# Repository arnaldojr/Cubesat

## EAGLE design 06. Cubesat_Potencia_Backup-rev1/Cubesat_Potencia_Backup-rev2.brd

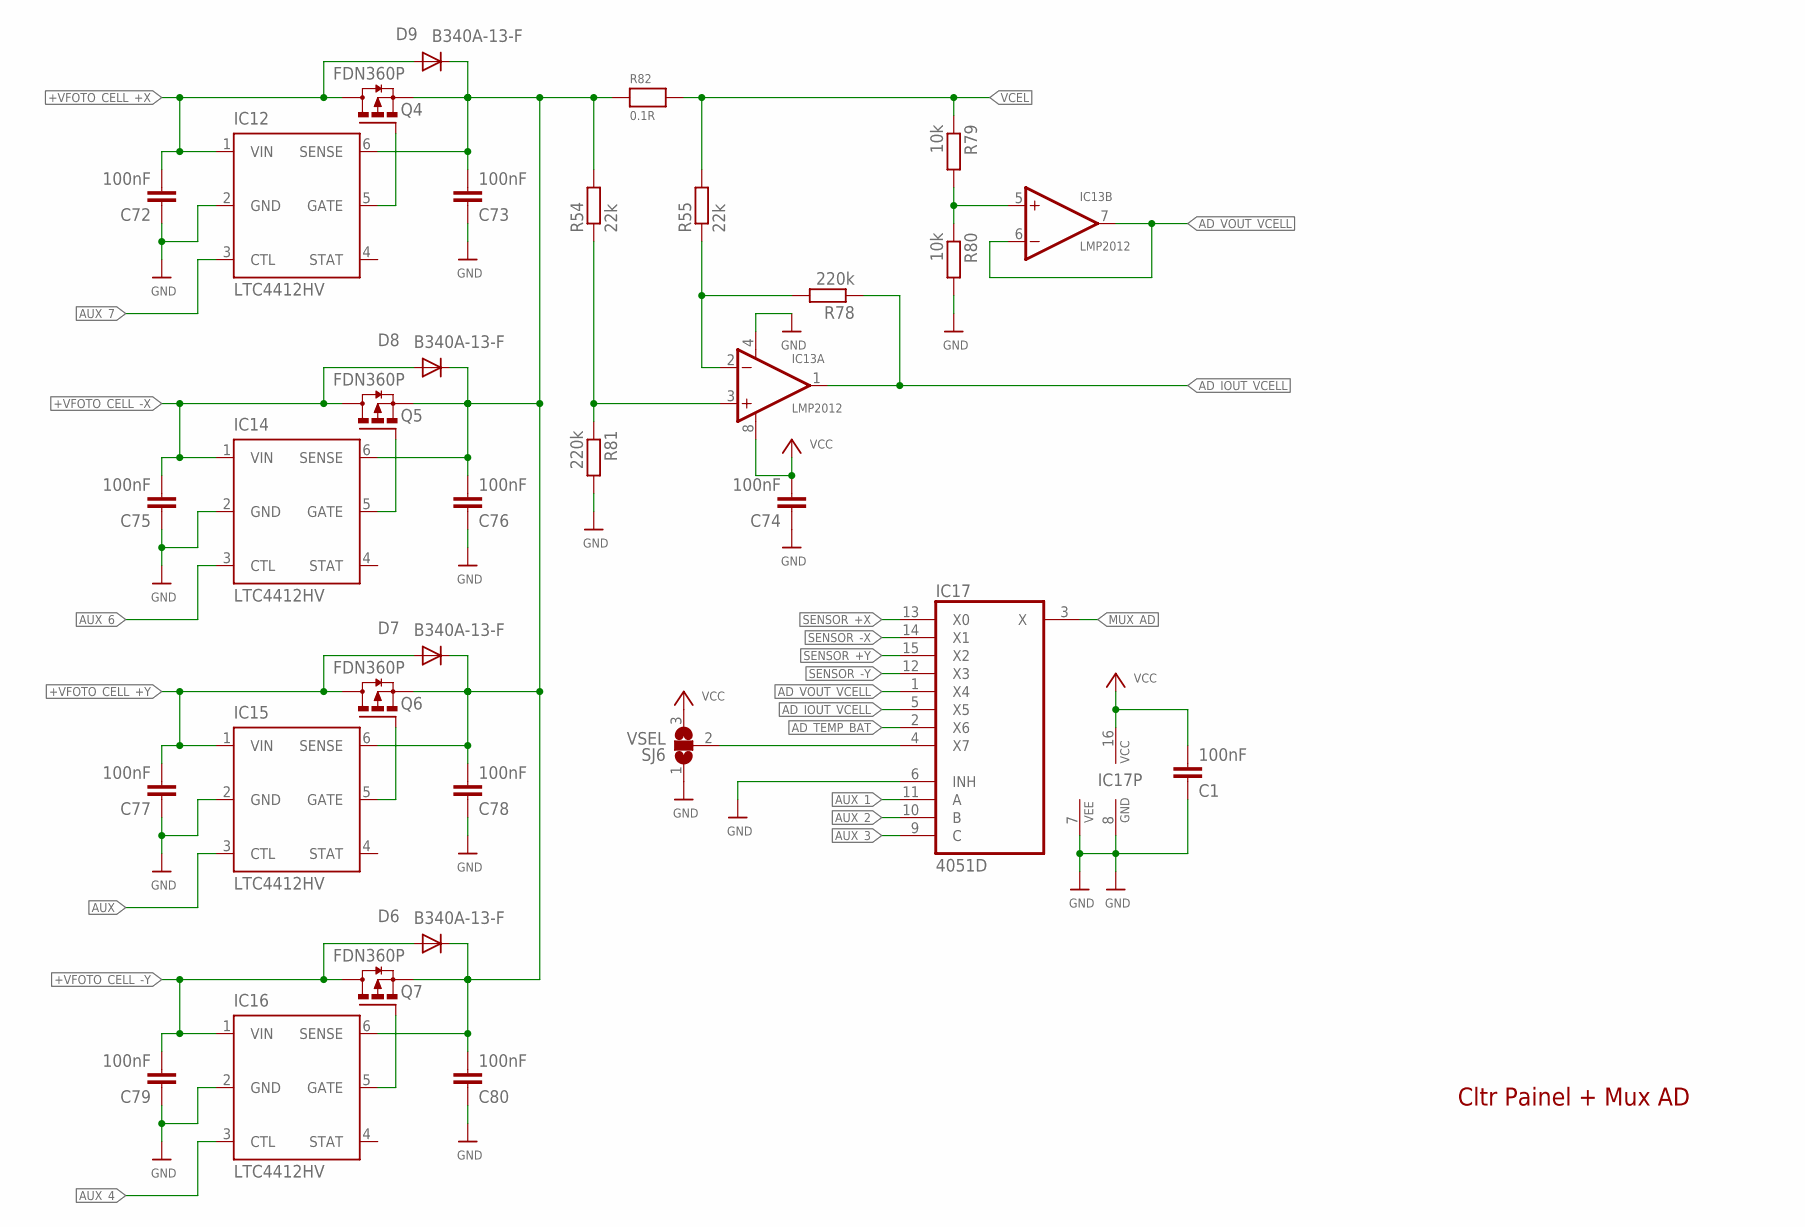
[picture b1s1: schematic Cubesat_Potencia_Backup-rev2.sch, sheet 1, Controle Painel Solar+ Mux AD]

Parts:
C1, C72, C73, C74, C75, C76, C77, C78, C79, C80: 100nF; C0805
D6, D7, D8, D9: B340A-13-F; DO214AC
IC12, IC14, IC15, IC16: LTC4412HV; TSOT23-6
IC13: LMP2012; MSOP08; MPN OPA2237EA/250
IC17: 4051D; SO16
Q4, Q5, Q6, Q7: FDN360P; SUPER-SOT3
R54, R55: 22k; M0805
R78, R81: 220k; M0805
R79, R80: 10k; M0805
R82: 0.1R; _2818
SJ6: VSEL; SJ_2

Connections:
+VFOTO_CELL_+X: C72.2, D9.A, IC12.1 (VIN), Q4.3 (D); also elsewhere on the board
+VFOTO_CELL_+Y: C77.2, D7.A, IC15.1 (VIN), Q6.3 (D); also elsewhere on the board
+VFOTO_CELL_-X: C75.2, D8.A, IC14.1 (VIN), Q5.3 (D); also elsewhere on the board
+VFOTO_CELL_-Y: C79.2, D6.A, IC16.1 (VIN), Q7.3 (D); also elsewhere on the board
AD_IOUT_VCELL: IC13.1 (OUT), IC17.5 (X5), R78.1
AD_TEMP_BAT: IC17.2 (X6); also elsewhere on the board
AD_VOUT_VCELL: IC13.6 (-IN), IC13.7 (OUT), IC17.1 (X4)
AUX: IC15.3 (CTL); also elsewhere on the board
AUX_1: IC17.11 (A); also elsewhere on the board
AUX_2: IC17.10 (B); also elsewhere on the board
AUX_3: IC17.9 (C); also elsewhere on the board
AUX_4: IC16.3 (CTL); also elsewhere on the board
AUX_6: IC14.3 (CTL); also elsewhere on the board
AUX_7: IC12.3 (CTL); also elsewhere on the board
GND: C1.1, C72.1, C73.1, C74.1, C75.1, C76.1, C77.1, C78.1, C79.1, C80.1, IC12.2 (GND), IC13.4 (V-), IC14.2 (GND), IC15.2 (GND), IC16.2 (GND), IC17.6 (INH), IC17.7 (VEE), IC17.8 (GND), R80.2, R81.2, SJ6.1; also elsewhere on the board
MUX_AD: IC17.3 (X); also elsewhere on the board
unnamed: IC12.5 (GATE), Q4.1 (G)
unnamed: IC13.5 (+IN), R79.2, R80.1
unnamed: IC13.2 (-IN), R55.1, R78.2
unnamed: IC13.3 (+IN), R54.1, R81.1
unnamed: C73.2, C76.2, C78.2, C80.2, D6.C, D7.C, D8.C, D9.C, IC12.6 (SENSE), IC14.6 (SENSE), IC15.6 (SENSE), IC16.6 (SENSE), Q4.2 (S), Q5.2 (S), Q6.2 (S), Q7.2 (S), R54.2, R82.1
unnamed: IC17.4 (X7), SJ6.2
unnamed: IC14.5 (GATE), Q5.1 (G)
unnamed: IC15.5 (GATE), Q6.1 (G)
unnamed: IC16.5 (GATE), Q7.1 (G)
SENSOR_+X: IC17.13 (X0); also elsewhere on the board
SENSOR_+Y: IC17.15 (X2); also elsewhere on the board
SENSOR_-X: IC17.14 (X1); also elsewhere on the board
SENSOR_-Y: IC17.12 (X3); also elsewhere on the board
VCC: C1.2, C74.2, IC13.8 (V+), IC17.16 (VCC), SJ6.3; also elsewhere on the board
VCEL: R55.2, R79.1, R82.2; also elsewhere on the board

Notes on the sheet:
Cltr Painel + Mux AD

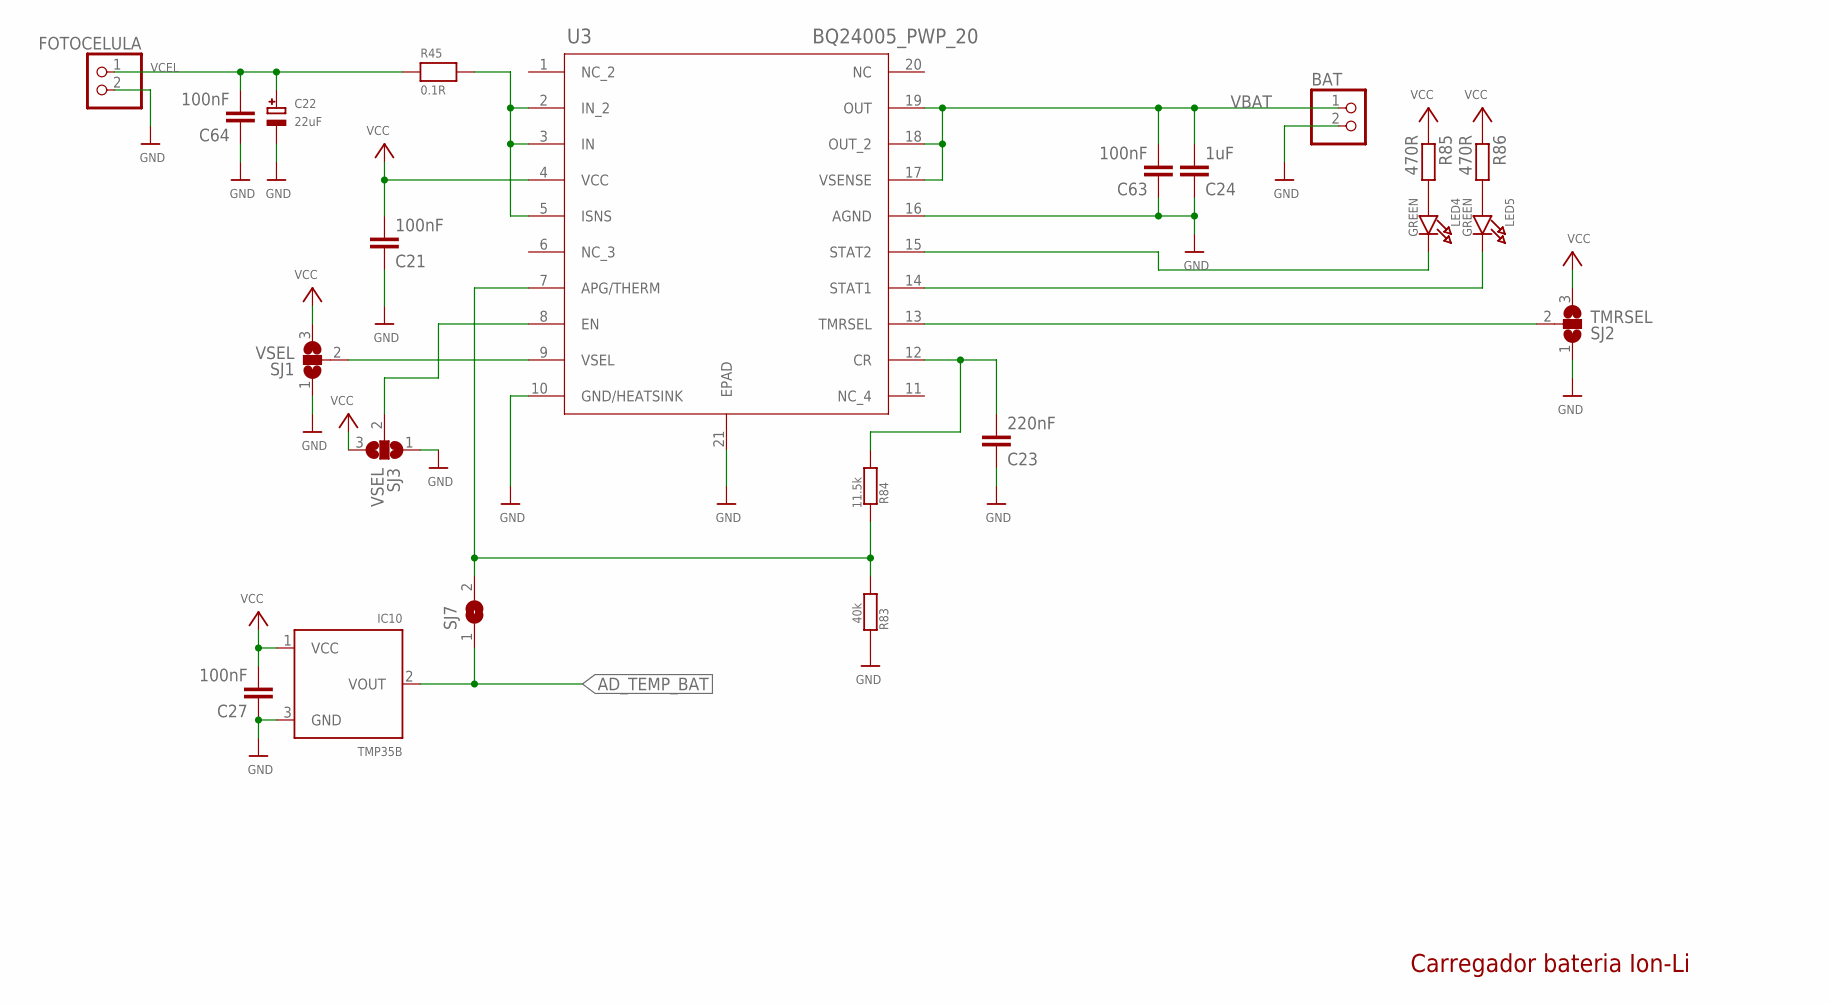
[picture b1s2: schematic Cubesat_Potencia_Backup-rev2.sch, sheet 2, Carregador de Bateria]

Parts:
BAT: HEADER-1X2; 1X02_OVAL
C21, C27, C63, C64: 100nF; C0805
C22: 22uF; EIA6032-28/C-R
C23: 220nF; C0805
C24: 1uF; C0805
FOTOCELULA: HEADER-1X2; 1X02_OVAL
IC10: TMP35B; TO92-LINE
LED4, LED5: GREEN; CHIPLED_0805
R45: 0.1R; _2818
R83: 40k; M0805
R84: 11.5k; M0805
R85, R86: 470R; M0805
SJ1, SJ3: VSEL; SJ_2
SJ2: TMRSEL; SJ_2
SJ7: SOLDERJUMPER; SOLDERJUMPER_ARROW_NOPASTE
U3: BQ24005_PWP_20; PWP20_2P4X3P4

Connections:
AD_TEMP_BAT: IC10.2 (VOUT), SJ7.1; also elsewhere on the board
GND: BAT.2, C21.1, C22.-, C23.1, C24.1, C27.1, C63.1, C64.1, FOTOCELULA.2, IC10.3 (GND), R83.2, SJ1.1, SJ2.1, SJ3.1, U3.10 (GND/HEATSINK), U3.16 (AGND), U3.21 (EPAD); also elsewhere on the board
unnamed: SJ3.2, U3.8 (EN)
unnamed: R45.2, U3.2 (IN_2), U3.3 (IN), U3.5 (ISNS)
unnamed: SJ2.2, U3.13 (TMRSEL)
unnamed: SJ1.2, U3.9 (VSEL)
unnamed: C23.2, R84.1, U3.12 (CR)
unnamed: LED4.A, R85.2
unnamed: R83.1, R84.2, SJ7.2, U3.7 (APG/THERM)
unnamed: LED5.A, R86.2
unnamed: LED5.C, U3.14 (STAT1)
unnamed: LED4.C, U3.15 (STAT2)
VBAT: BAT.1, C24.2, C63.2, U3.17 (VSENSE), U3.18 (OUT_2), U3.19 (OUT); also elsewhere on the board
VCC: C21.2, C27.2, IC10.1 (VCC), R85.1, R86.1, SJ1.3, SJ2.3, SJ3.3, U3.4 (VCC); also elsewhere on the board
VCEL: C22.+, C64.2, FOTOCELULA.1, R45.1; also elsewhere on the board

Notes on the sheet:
Carregador bateria Ion-Li

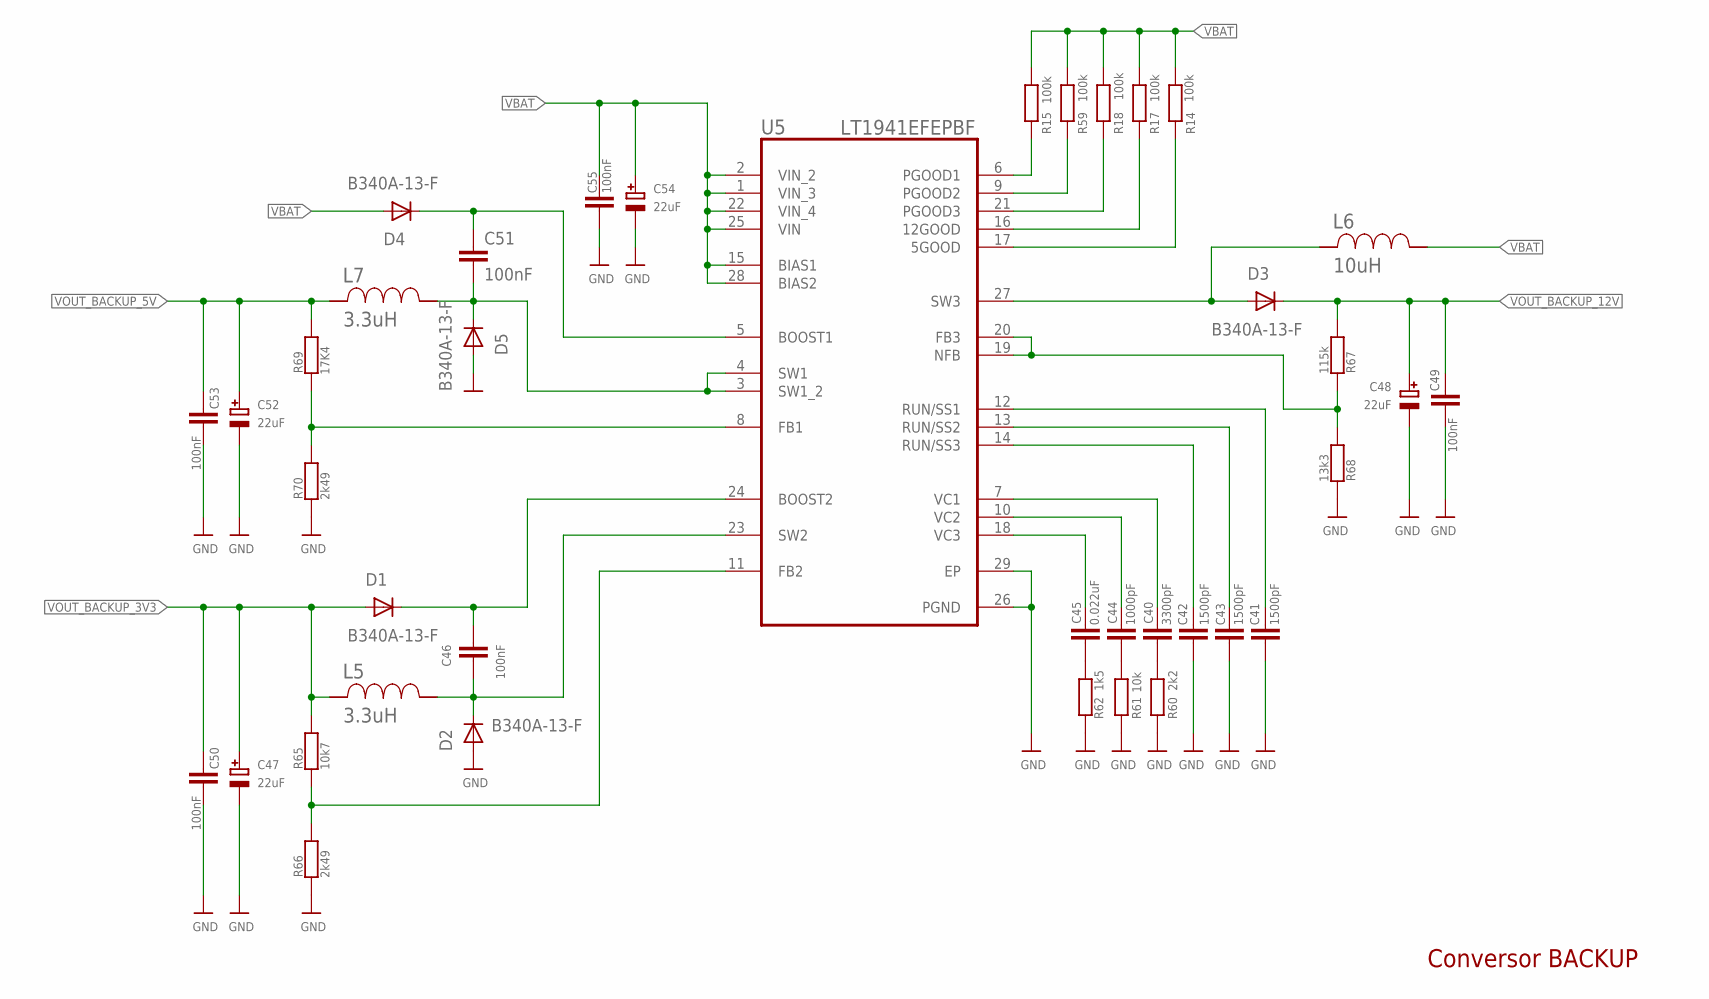
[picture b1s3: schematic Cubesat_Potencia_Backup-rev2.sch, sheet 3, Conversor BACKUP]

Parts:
C40: 3300pF; C0805
C41, C42, C43: 1500pF; C0805
C44: 1000pF; C0805
C45: 0.022uF; C0805
C46, C49, C50, C53, C55: 100nF; C0805
C47, C48, C52, C54: 22uF; EIA6032-28/C-R
C51: 100nF; C1210
D1, D2, D3, D4, D5: B340A-13-F; DO214AC
L5, L7: 3.3uH; SRR6038
L6: 10uH; SRR6038
R14, R15, R17, R18, R59: 100k; M0805
R60: 2k2; M0805
R61: 10k; M0805
R62: 1k5; M0805
R65: 10k7; M0805
R66, R70: 2k49; M0805
R67: 115k; M0805
R68: 13k3; M0805
R69: 17K4; M0805
U5: LT1941EFEPBF; SOP65P640X120-29N

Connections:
BOOST1: C51.1, D4.C, U5.5 (BOOST1)
FB1: R69.2, R70.1, U5.8 (FB1)
FB2: R65.2, R66.1, U5.11 (FB2)
FB3: R67.2, R68.1, U5.19 (NFB), U5.20 (FB3)
GND: C41.2, C42.2, C43.2, C47.-, C48.-, C49.2, C50.2, C52.-, C53.2, C54.-, C55.2, D2.A, D5.A, R60.1, R61.1, R62.1, R66.2, R68.2, R70.2, U5.26 (PGND), U5.29 (EP); also elsewhere on the board
unnamed: R14.2, U5.17 (5GOOD)
unnamed: R17.2, U5.16 (12GOOD)
unnamed: R18.2, U5.21 (PGOOD3)
unnamed: R59.2, U5.9 (PGOOD2)
unnamed: R15.2, U5.6 (PGOOD1)
unnamed: C41.1, U5.12 (RUN/SS1)
unnamed: C43.1, U5.13 (RUN/SS2)
unnamed: C42.1, U5.14 (RUN/SS3)
unnamed: C40.1, R60.2
unnamed: C44.2, U5.10 (VC2)
unnamed: C45.2, U5.18 (VC3)
unnamed: C44.1, R61.2
unnamed: C45.1, R62.2
unnamed: C40.2, U5.7 (VC1)
unnamed: C46.1, D1.C, U5.24 (BOOST2)
SW1: C51.2, D5.C, L7.2, U5.3 (SW1_2), U5.4 (SW1)
SW2: C46.2, D2.C, L5.2, U5.23 (SW2)
SW3: D3.A, L6.1, U5.27 (SW3)
VBAT: C54.+, C55.1, D4.A, L6.2, R14.1, R15.1, R17.1, R18.1, R59.1, U5.1 (VIN_3), U5.2 (VIN_2), U5.15 (BIAS1), U5.22 (VIN_4), U5.25 (VIN), U5.28 (BIAS2); also elsewhere on the board
VOUT_BACKUP_3V3: C47.+, C50.1, D1.A, L5.1, R65.1; also elsewhere on the board
VOUT_BACKUP_5V: C52.+, C53.1, L7.1, R69.1; also elsewhere on the board
VOUT_BACKUP_12V: C48.+, C49.1, D3.C, R67.1; also elsewhere on the board

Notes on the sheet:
Conversor BACKUP

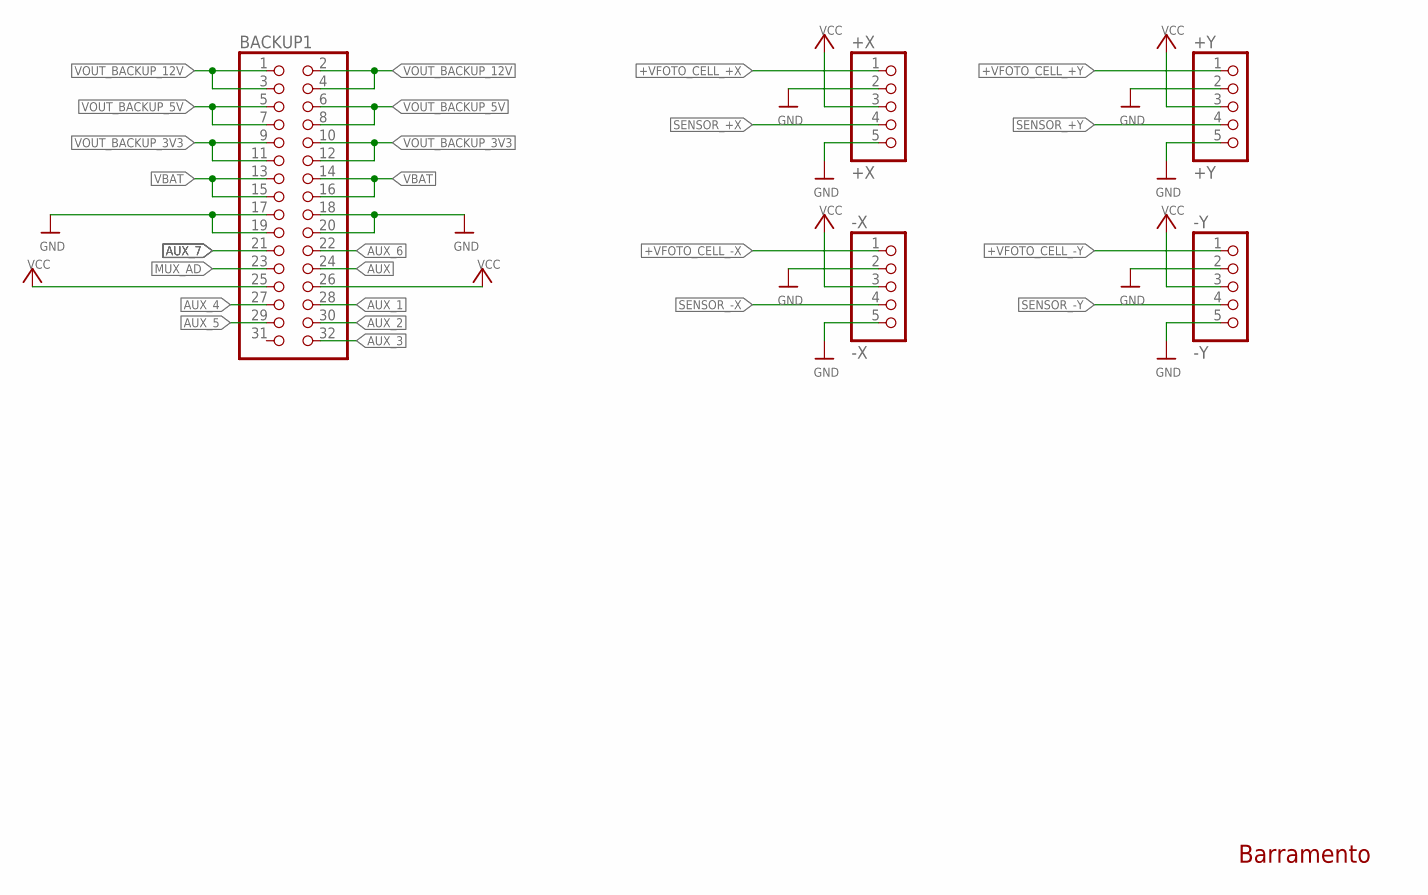
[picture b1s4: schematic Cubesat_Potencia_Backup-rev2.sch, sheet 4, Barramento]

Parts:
+X: +X; 1X05
+Y: +Y; 1X05
-X: -X; 1X05
-Y: -Y; 1X05
BACKUP1: PINHD-2X16; 2X16

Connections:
+VFOTO_CELL_+X: +X.1; also elsewhere on the board
+VFOTO_CELL_+Y: +Y.1; also elsewhere on the board
+VFOTO_CELL_-X: -X.1; also elsewhere on the board
+VFOTO_CELL_-Y: -Y.1; also elsewhere on the board
AUX: BACKUP1.24; also elsewhere on the board
AUX_1: BACKUP1.28; also elsewhere on the board
AUX_2: BACKUP1.30; also elsewhere on the board
AUX_3: BACKUP1.32; also elsewhere on the board
AUX_4: BACKUP1.27; also elsewhere on the board
AUX_5: BACKUP1.29
AUX_6: BACKUP1.22; also elsewhere on the board
AUX_7: BACKUP1.21; also elsewhere on the board
GND: +X.2, +X.5, +Y.2, +Y.5, -X.2, -X.5, -Y.2, -Y.5, BACKUP1.17, BACKUP1.18, BACKUP1.19, BACKUP1.20; also elsewhere on the board
MUX_AD: BACKUP1.23; also elsewhere on the board
SENSOR_+X: +X.4; also elsewhere on the board
SENSOR_+Y: +Y.4; also elsewhere on the board
SENSOR_-X: -X.4; also elsewhere on the board
SENSOR_-Y: -Y.4; also elsewhere on the board
VBAT: BACKUP1.13, BACKUP1.14, BACKUP1.15, BACKUP1.16; also elsewhere on the board
VCC: +X.3, +Y.3, -X.3, -Y.3, BACKUP1.25, BACKUP1.26; also elsewhere on the board
VOUT_BACKUP_3V3: BACKUP1.9, BACKUP1.10, BACKUP1.11, BACKUP1.12; also elsewhere on the board
VOUT_BACKUP_5V: BACKUP1.5, BACKUP1.6, BACKUP1.7, BACKUP1.8; also elsewhere on the board
VOUT_BACKUP_12V: BACKUP1.1, BACKUP1.2, BACKUP1.3, BACKUP1.4; also elsewhere on the board

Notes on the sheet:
Barramento

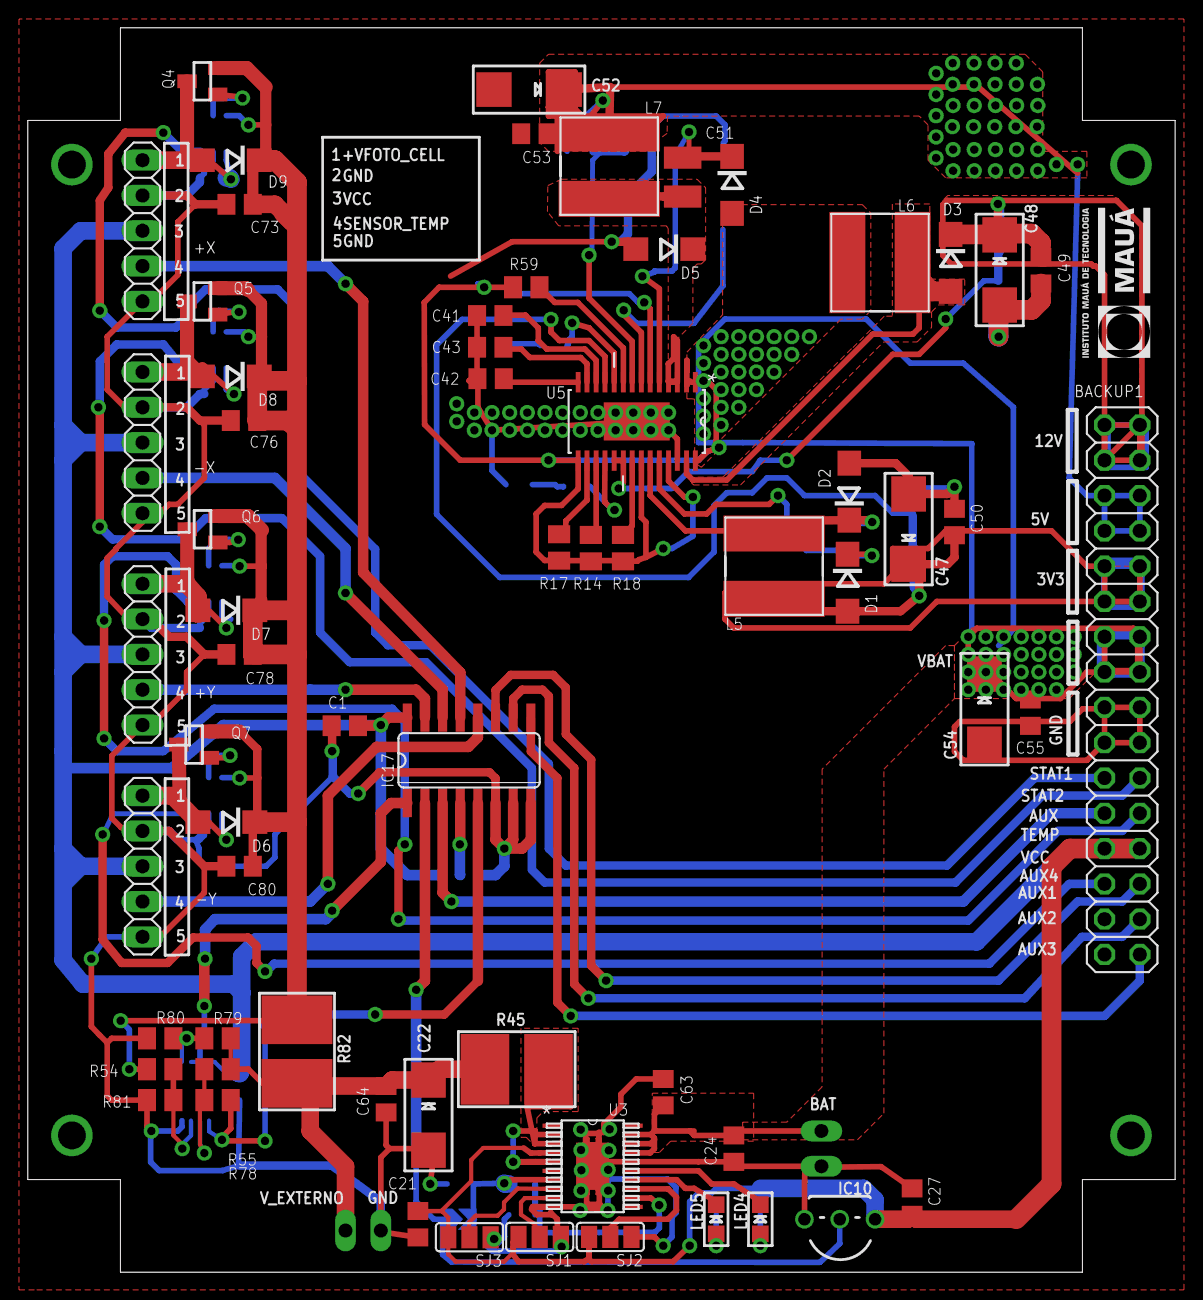
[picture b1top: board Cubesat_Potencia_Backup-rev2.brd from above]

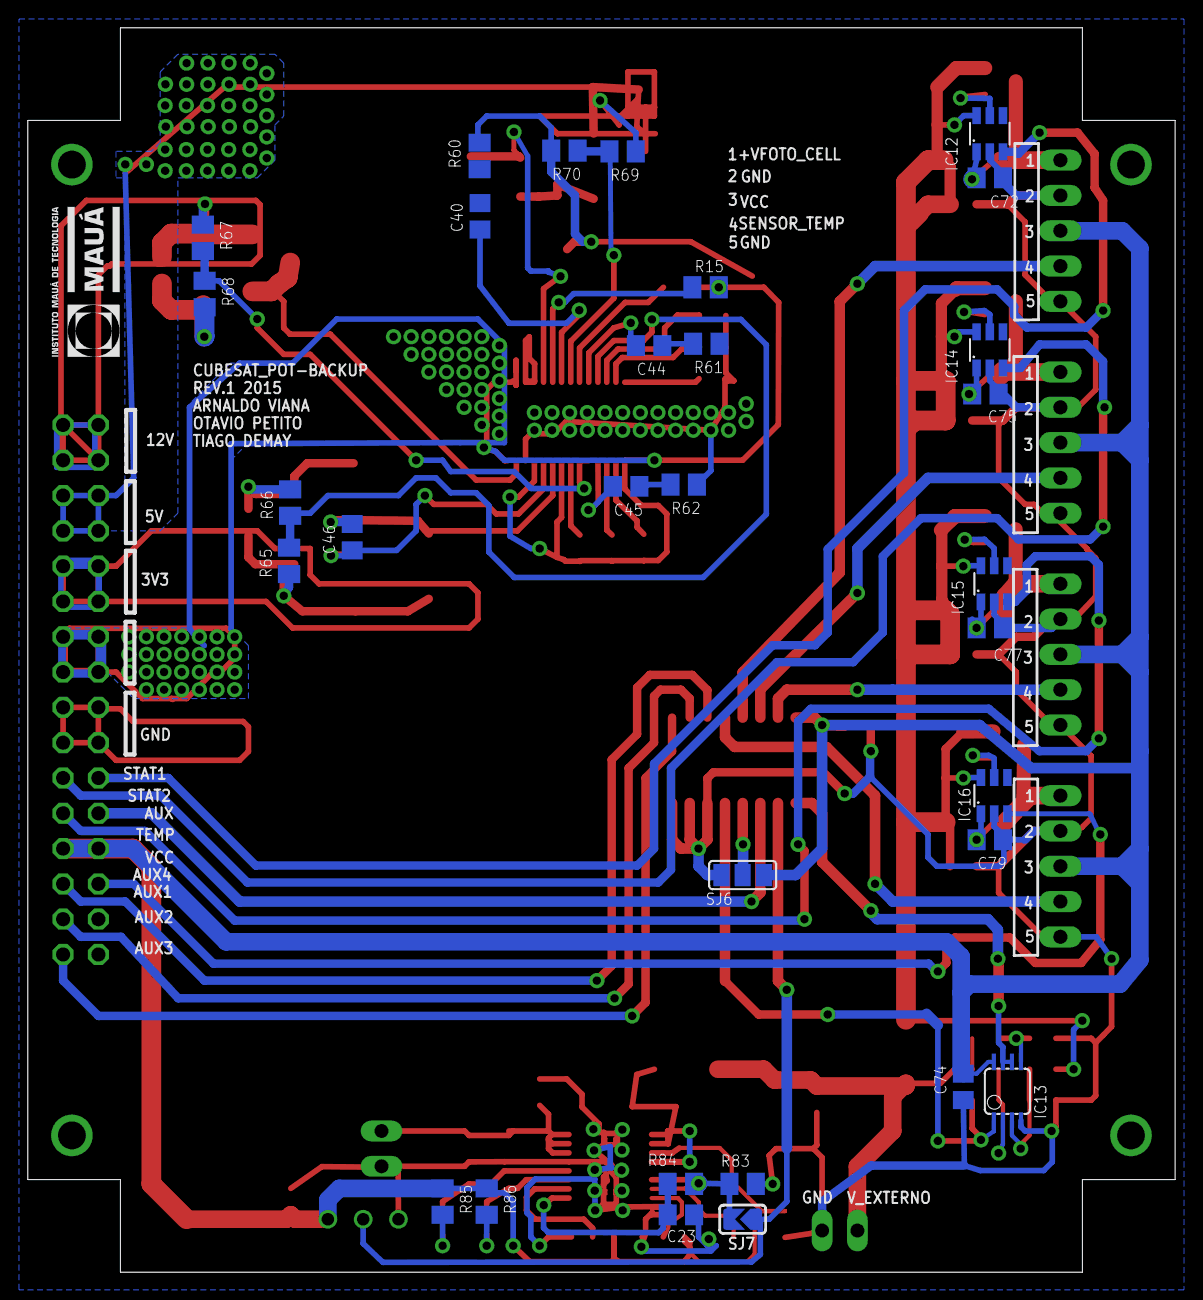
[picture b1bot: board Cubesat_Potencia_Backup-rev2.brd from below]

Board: 2 copper layers, 82.5 x 89.5 mm, 100 parts (32 on the bottom side), 67 nets.

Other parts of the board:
U$2, U$112: LOGO_MAUA

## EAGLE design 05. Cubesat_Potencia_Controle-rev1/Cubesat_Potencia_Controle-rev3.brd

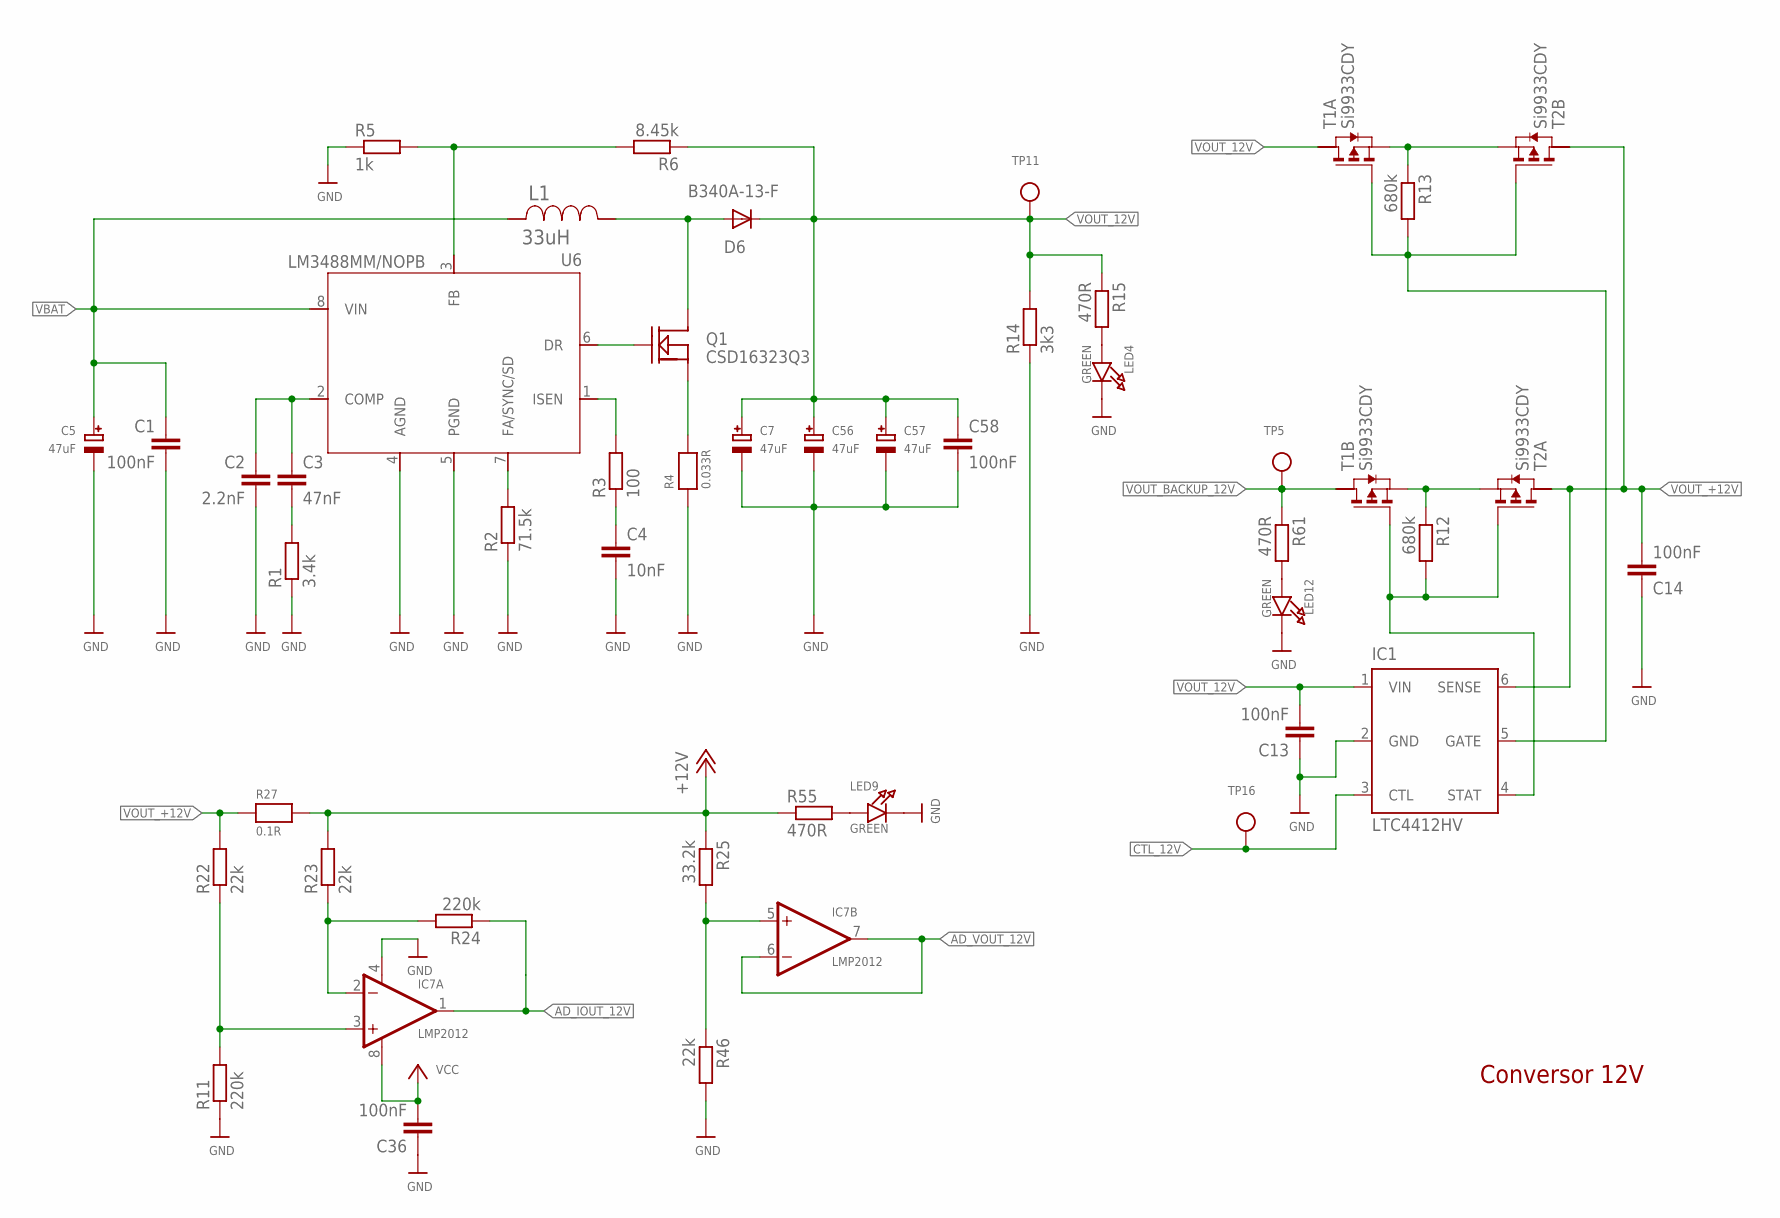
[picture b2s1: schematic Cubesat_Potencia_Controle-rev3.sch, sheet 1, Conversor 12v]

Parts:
C1, C13, C14, C36, C58: 100nF; C0805
C2: 2.2nF; C0805
C3: 47nF; C0805
C4: 10nF; C0805
C5, C7, C56, C57: 47uF; EIA6032-28/C-R
D6: B340A-13-F; DO214AC
IC1: LTC4412HV; TSOT23-6
IC7: LMP2012; MSOP08; MPN OPA2237EA/250
L1: 33uH; SDR1307
LED4, LED9, LED12: GREEN; CHIPLED_0805
Q1: CSD16323Q3; TRANS_NEXFET_Q3
R1: 3.4k; M0805
R2: 71.5k; M0805
R3: 100; M0805
R4: 0.033R; _2818
R5: 1k; M0805
R6: 8.45k; M0805
R11, R24: 220k; M0805
R12, R13: 680k; M0805
R14: 3k3; M0805
R15, R55, R61: 470R; M0805
R22, R23, R46: 22k; M0805
R25: 33.2k; M0805
R27: 0.1R; _2818
T1, T2: Si9933CDY; SO8
TP5, TP11, TP16: TESTPOINT0.1"; 1X01_ROUND
U6: LM3488MM/NOPB; MUA08A

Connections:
6: D6.A, L1.2, Q1.5 (DRAIN)
+12V: R23.2, R25.1, R27.2, R55.1; also elsewhere on the board
AD_IOUT_12V: IC7.1 (OUT), R24.1; also elsewhere on the board
AD_VOUT_12V: IC7.6 (-IN), IC7.7 (OUT); also elsewhere on the board
CTL_12V: IC1.3 (CTL), TP16.1; also elsewhere on the board
GND: C1.2, C2.2, C4.2, C5.-, C7.-, C13.1, C14.1, C36.1, C56.-, C57.-, C58.2, IC1.2 (GND), IC7.4 (V-), LED4.C, LED9.C, LED12.C, R1.1, R2.1, R4.1, R5.1, R11.1, R14.1, R46.2, U6.4 (AGND), U6.5 (PGND); also elsewhere on the board
unnamed: Q1.1 (SOURCE), R4.2
unnamed: Q1.4 (GATE), U6.6 (DR)
unnamed: R2.2, U6.7 (FA/SYNC/SD)
unnamed: R3.2, U6.1 (ISEN)
unnamed: C4.1, R3.1
unnamed: R5.2, R6.2, U6.3 (FB)
unnamed: C2.1, C3.1, U6.2 (COMP)
unnamed: C3.2, R1.2
unnamed: R13.1, T1.1 (S), T2.3 (S)
unnamed: R12.1, T1.3 (S), T2.1 (S)
unnamed: IC1.4 (STAT), R12.2, T1.4 (G), T2.2 (G)
unnamed: LED4.A, R15.2
unnamed: IC7.5 (+IN), R25.2, R46.1
unnamed: IC7.2 (-IN), R23.1, R24.2
unnamed: IC7.3 (+IN), R11.2, R22.1
unnamed: LED9.A, R55.2
unnamed: LED12.A, R61.2
STAT_12V: IC1.5 (GATE), R13.2, T1.2 (G), T2.4 (G)
VBAT: C1.1, C5.+, L1.1, U6.8 (VIN); also elsewhere on the board
VCC: C36.2, IC7.8 (V+); also elsewhere on the board
VOUT_12V: C7.+, C13.2, C56.+, C57.+, C58.1, D6.C, IC1.1 (VIN), R6.1, R14.2, R15.1, T1.7 (D), TP11.1
VOUT_+12V: C14.2, IC1.6 (SENSE), R22.2, R27.1, T2.6 (D), T2.7 (D)
VOUT_BACKUP_12V: R61.1, T1.6 (D), TP5.1; also elsewhere on the board

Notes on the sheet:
Conversor 12V

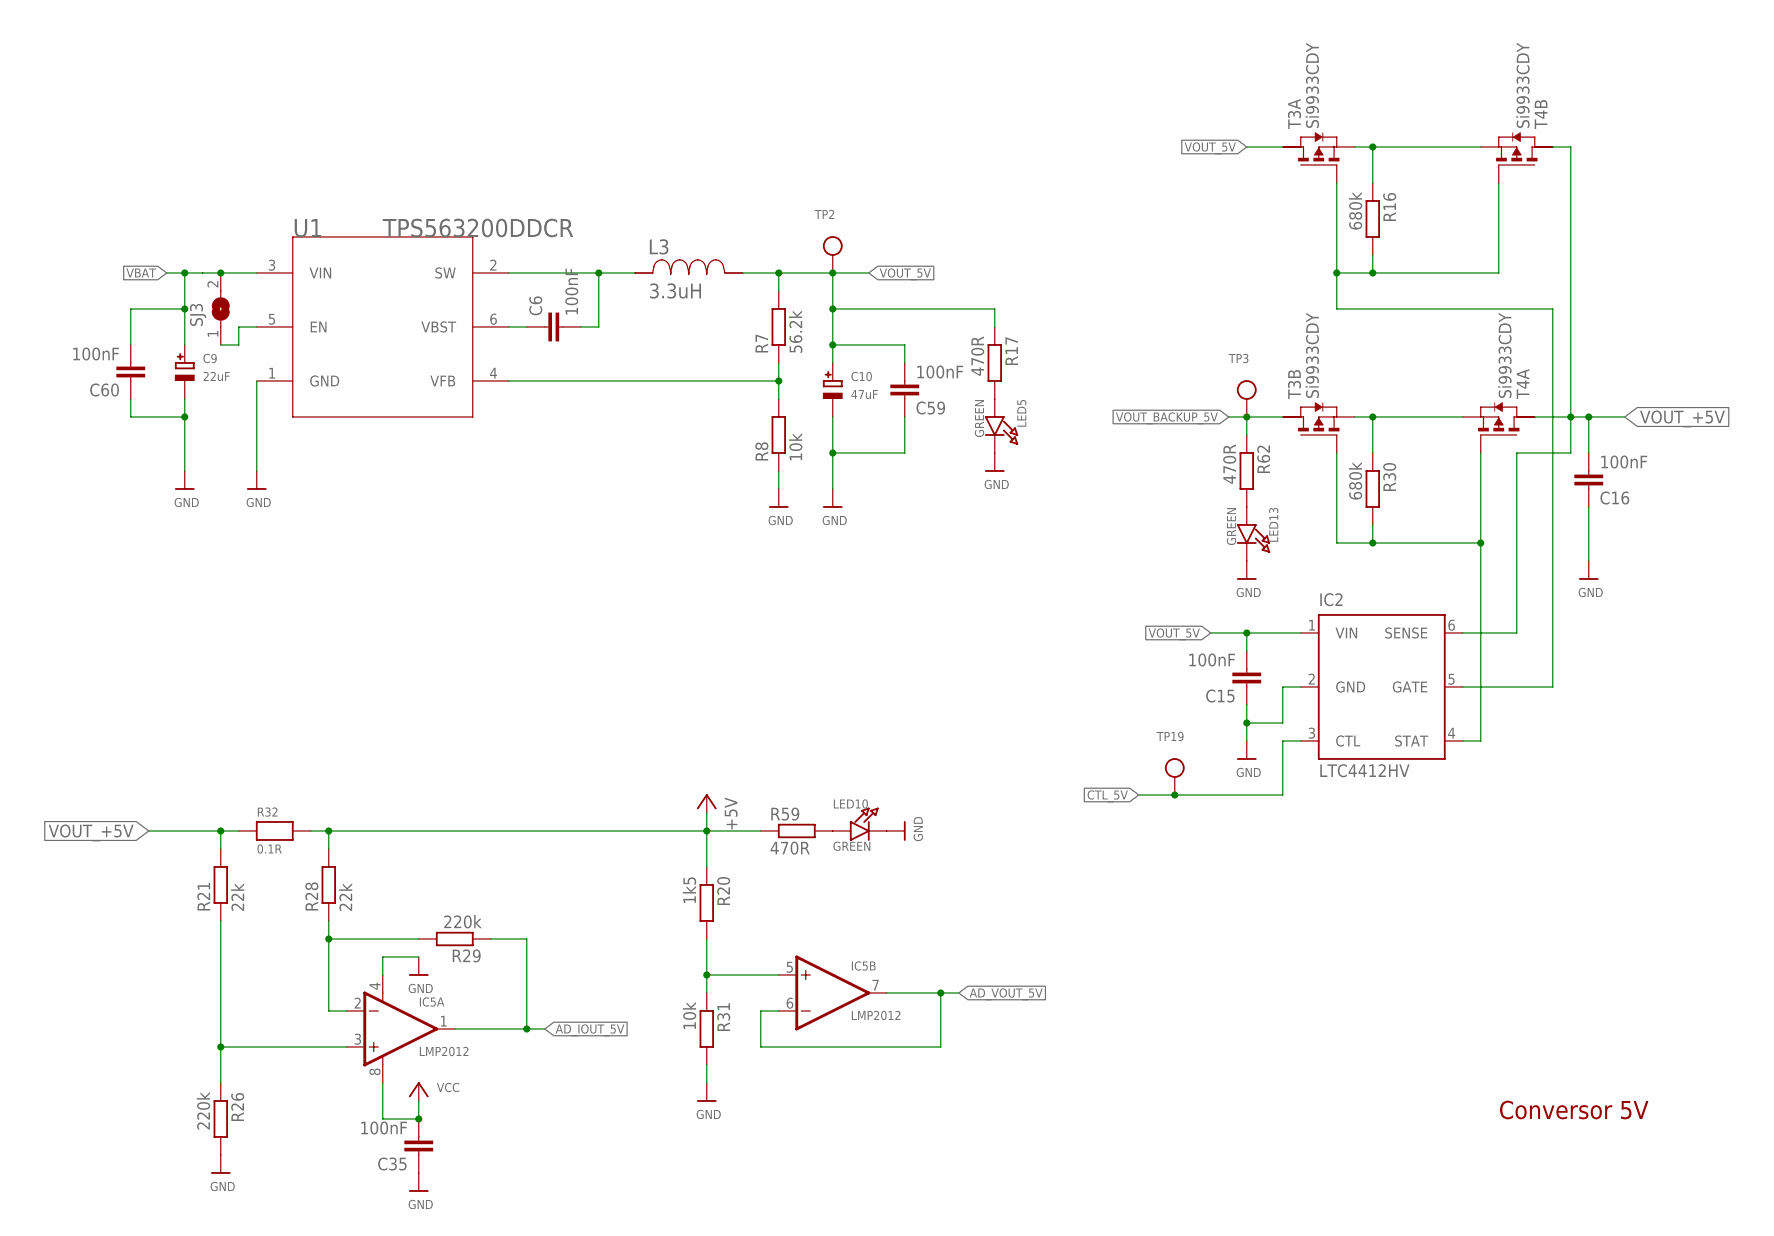
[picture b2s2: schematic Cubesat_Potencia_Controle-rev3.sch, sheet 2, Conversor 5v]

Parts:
C6, C15, C16, C35, C59, C60: 100nF; C0805
C9: 22uF; EIA6032-28/C-R
C10: 47uF; EIA6032-28/C-R
IC2: LTC4412HV; TSOT23-6
IC5: LMP2012; MSOP08; MPN OPA2237EA/250
L3: 3.3uH; SRR6038
LED5, LED10, LED13: GREEN; CHIPLED_0805
R7: 56.2k; M0805
R8, R31: 10k; M0805
R16, R30: 680k; M0805
R17, R59, R62: 470R; M0805
R20: 1k5; M0805
R21, R28: 22k; M0805
R26, R29: 220k; M0805
R32: 0.1R; _2818
SJ3: SOLDERJUMPER; SOLDERJUMPER_ARROW_NOPASTE
T3, T4: Si9933CDY; SO8
TP2, TP3, TP19: TESTPOINT0.1"; 1X01_ROUND
U1: TPS563200DDCR; DDC0006A

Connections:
+5V: R20.1, R28.2, R32.2, R59.1; also elsewhere on the board
AD_IOUT_5V: IC5.1 (OUT), R29.1; also elsewhere on the board
AD_VOUT_5V: IC5.6 (-IN), IC5.7 (OUT); also elsewhere on the board
CTL_5V: IC2.3 (CTL), TP19.1; also elsewhere on the board
GND: C9.-, C10.-, C15.1, C16.1, C35.1, C59.1, C60.1, IC2.2 (GND), IC5.4 (V-), LED5.C, LED10.C, LED13.C, R8.1, R26.2, R31.2, U1.1 (GND); also elsewhere on the board
unnamed: C6.1, U1.6 (VBST)
unnamed: C6.2, L3.1, U1.2 (SW)
unnamed: R7.1, R8.2, U1.4 (VFB)
unnamed: R16.1, T3.1 (S), T4.3 (S)
unnamed: R30.1, T3.3 (S), T4.1 (S)
unnamed: IC2.4 (STAT), R30.2, T3.4 (G), T4.2 (G)
unnamed: IC5.5 (+IN), R20.2, R31.1
unnamed: LED5.A, R17.2
unnamed: IC5.2 (-IN), R28.1, R29.2
unnamed: IC5.3 (+IN), R21.1, R26.1
unnamed: LED10.A, R59.2
unnamed: LED13.A, R62.2
unnamed: SJ3.1, U1.5 (EN)
STAT_5V: IC2.5 (GATE), R16.2, T3.2 (G), T4.4 (G)
VBAT: C9.+, C60.2, SJ3.2, U1.3 (VIN); also elsewhere on the board
VCC: C35.2, IC5.8 (V+); also elsewhere on the board
VOUT_5V: C10.+, C15.2, C59.2, IC2.1 (VIN), L3.2, R7.2, R17.1, T3.7 (D), TP2.1
VOUT_+5V: C16.2, IC2.6 (SENSE), R21.2, R32.1, T4.6 (D), T4.7 (D)
VOUT_BACKUP_5V: R62.1, T3.6 (D), TP3.1; also elsewhere on the board

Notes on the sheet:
Conversor 5V

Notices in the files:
parts and their libraries:
junior: This work is placed in the public domain, and may be freely used for commercial and non-commercial work with the following conditions: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
